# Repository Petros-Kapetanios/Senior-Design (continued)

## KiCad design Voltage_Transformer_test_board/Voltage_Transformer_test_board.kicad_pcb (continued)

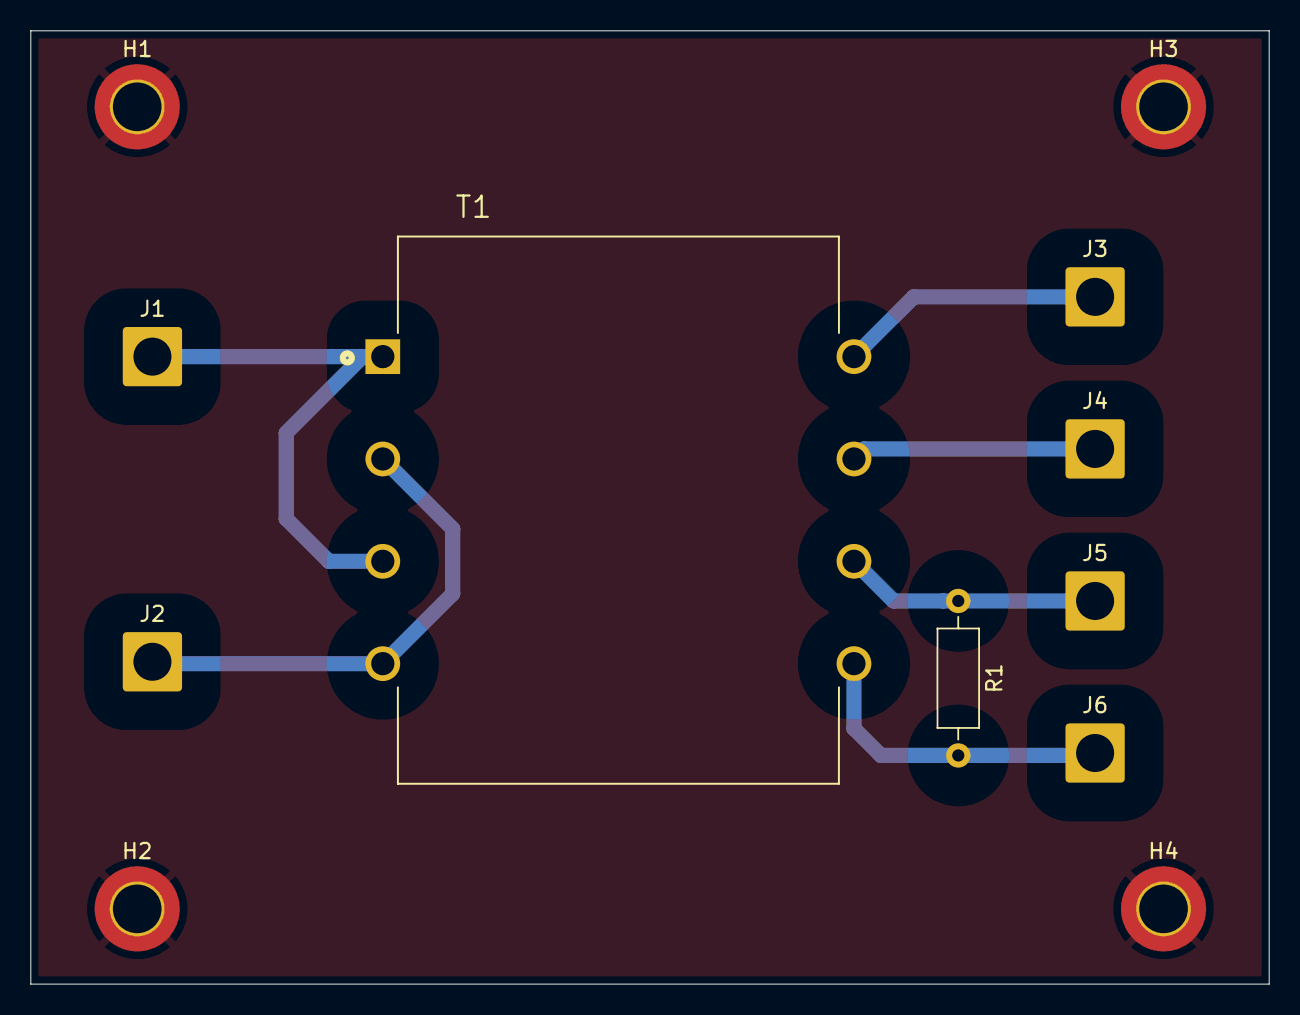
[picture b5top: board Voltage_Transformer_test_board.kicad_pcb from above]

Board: 2 copper layers, 81.4 x 62.7 mm, 12 parts (0 on the bottom side), 7 nets.

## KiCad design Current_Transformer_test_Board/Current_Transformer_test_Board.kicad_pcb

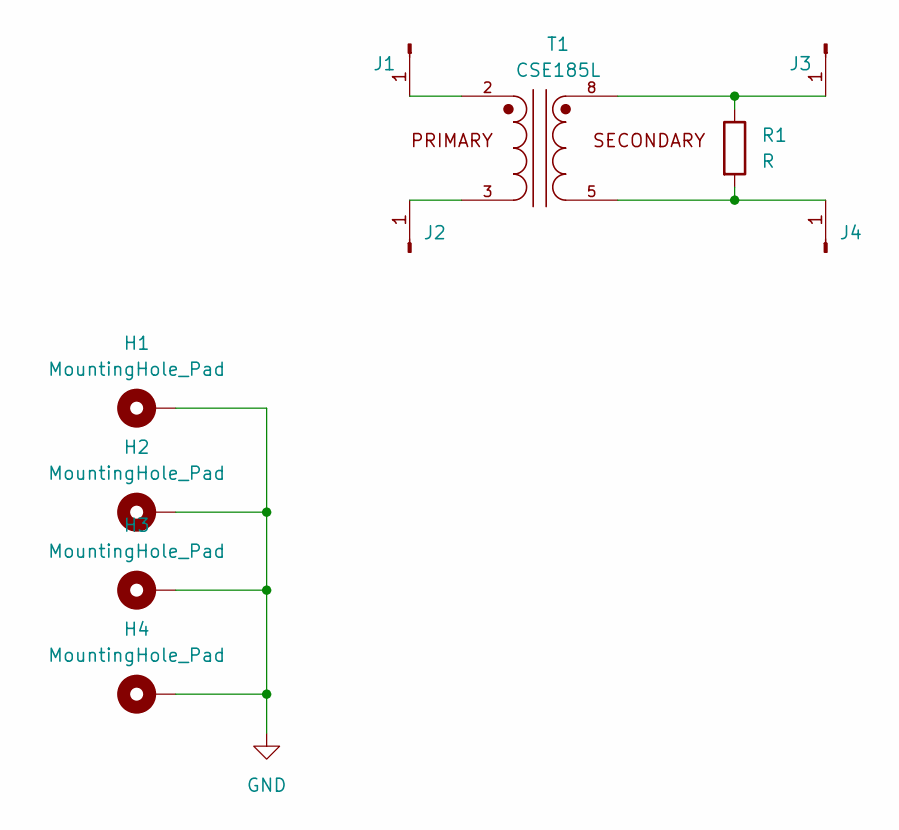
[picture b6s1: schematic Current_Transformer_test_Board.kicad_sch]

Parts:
H1, H2, H3, H4: MountingHole_Pad; MountingHole_3.2mm_M3_DIN965_Pad_TopBottom
J1, J2, J3, J4: Conn_01x01_Pin; SolderWire-2sqmm_1x01_D2mm_OD3.9mm
R1: R; R_Axial_DIN0207_L6.3mm_D2.5mm_P10.16mm_Horizontal
T1: CSE185L; XFMR_CSE185L; PARTREV N/A

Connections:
GND: H1.1, H2.1, H3.1, H4.1
unnamed: J1.1, T1.2
unnamed: J2.1, T1.3
unnamed: J3.1, R1.1, T1.8
unnamed: J4.1, R1.2, T1.5

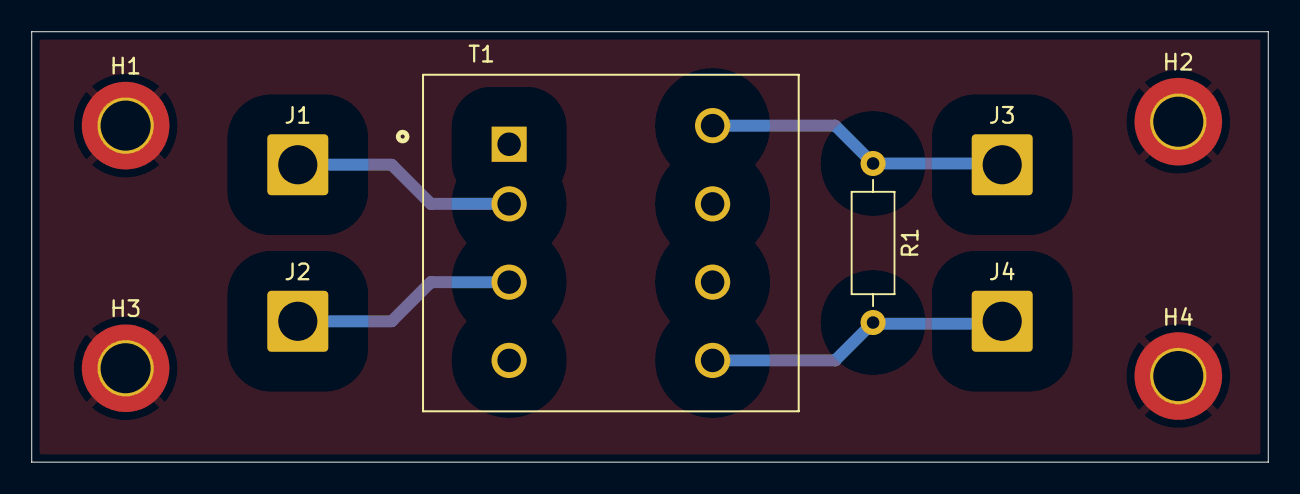
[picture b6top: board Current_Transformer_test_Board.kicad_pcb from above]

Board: 2 copper layers, 79.0 x 27.5 mm, 10 parts (0 on the bottom side), 5 nets.

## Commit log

2025-04-28 Create j
2025-05-15 Create Final_Board-v3D\
2025-05-15 Rename Final_Board-v3D\ to Final_Board-v3D/V3D
